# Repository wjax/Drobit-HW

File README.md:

# Drobit-HW
 This repository contains the electronic design and BOM files of the Drobit HW ecosystem.

 Drobit is a PPK (Post Processing Kinematics) solution for the UAV industry. Drobit allows to precisely geotag pictures taken by a camera on board the UAV allowing GCP-free (ground control point) photogrammetry surveys.

 Drobit HW ecosystem is:
 * Drobit Main board
    * Intel Edison CPU
    * Dual-Freq GNSS Board from ComNav
    * 9Dof IMU
    * Batttery management 
 * Drobit Hotshoe board
    * Camera flash signal conditioning
    * 9Dof IMU 
 * Optional: External Button-LED board for cases
 * Optional: Micro connector breakboard

 ## History
 Drobit was created in 2016 by Jose Martinez Rubio and Jesús Alvarez in order to overcome one of the main limitations when doing UAV Photogrammetry applied to big survey areas.... the manual positioning of GCPs.

 Drobit has been used too as *Drobit Inspector* for Civil infrastructure inspection.

 As of today, Drobit has finished its commercial life and we decided to opensource both HW and SW.

 ## Theory of operation
 The idea behind drobit is to provide aerial imagery with super precise WGS84 coordinates of the lens nodal point. If that's the case, photogrammetry software like Agisoft Metashaper or Pix4D can reconstruct the terrain 3D model with centimeter accuracy (with no GCP).

 In order to do that Drobit incorporates a Dual Frequency Survey grade GPS (ComNav 501G) with a Heical Harxon Dual frecuency Antenna that provides 20Hz RAW GNSS observations. We will use Differential GPS as the main source of precise geopositioning.
 It also contains two 9dof IMU, one in the drobit main board and one in the drobit hotshoe board.

 The hotshoe board will be inserted into the camera hotshoe and will provide precise timing for every picture by sensing the flash trigger.

 In a photogrammetry UAV flight, drobit will record GNSS observations (for later postprocessing PPK) and will capture IMU orientation for both drobit main board and hotshoe board.

## Post Processing (PPK and coordinates translation)
 Later, in the office, Drobit PPK Software will obtain precise GPS (WGS84) coordinates from the antenna phase center by resolving the PPK against a GNSS Base receiver (Drobit base or any other manufacturer base with Rinex, even a CORS).

 In order to obtain the nodal camera point position, Drobit PPK Software needs to translate the GNSS antenna coordinate using IMU values and X,Y,Z offsets.

 Once finished, pictures are geotagged and a file containing picture name and precise coordinates is generated.

 Drobit PPK Software creates an kmz for google earth that allows to see cameras oriented and located in 3d space.

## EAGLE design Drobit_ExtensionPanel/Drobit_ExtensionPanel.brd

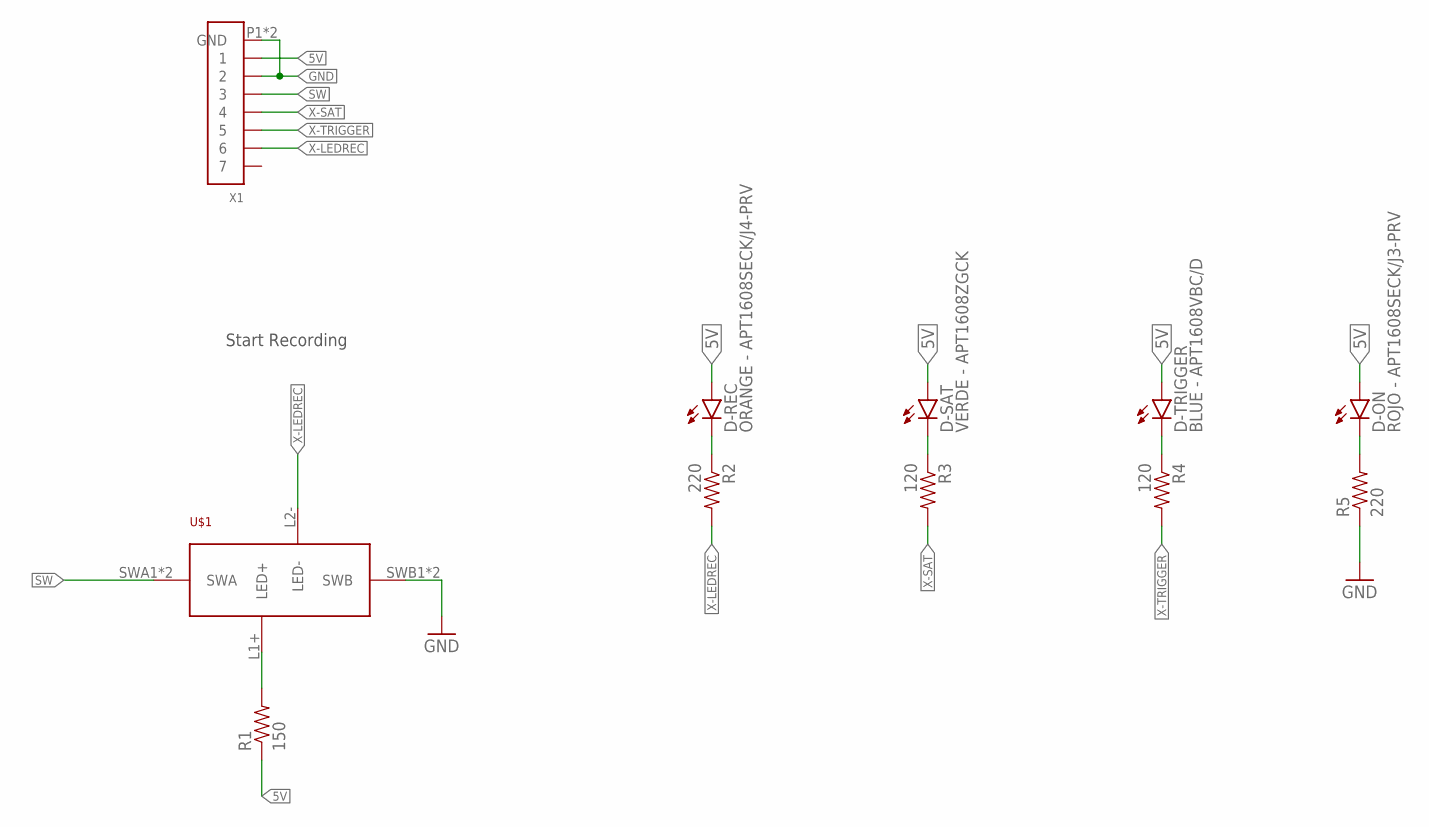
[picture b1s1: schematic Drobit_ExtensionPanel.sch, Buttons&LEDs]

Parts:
D-ON: ROJO - APT1608SECK/J3-PRV; LED3MM; PARTNO 604-APT1608SECKJ3PRV
D-REC: ORANGE - APT1608SECK/J4-PRV; LED3MM; PARTNO 604-APT1608SECKJ4PRV
D-SAT: VERDE - APT1608ZGCK; LED3MM; PARTNO 604-APT1608ZGCK
D-TRIGGER: BLUE - APT1608VBC/D; LED3MM; PARTNO 604-APT1608VBC/D
R1: 150; 1206
R2: 220; 1206; PARTNO 667-ERJ-3GEYJ181V
R3, R4: 120; 1206; PARTNO 667-ERJ-3EKF1050V
R5: 220; 1206; PARTNO 667-ERJ-3EKF82R0V
U$1: PUSH-LED; ITS13FV1ST
X1: CONN_7-1; JST-GH-7

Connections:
5V: D-ON.A, D-REC.A, D-SAT.A, D-TRIGGER.A, R1.1, X1.1
GND: R5.1, U$1.SWB1 (SWB), U$1.SWB2 (SWB), X1.2, X1.P1 (GND), X1.P2 (GND)
unnamed: R1.2, U$1.L1+ (LED+)
unnamed: D-ON.K (C), R5.2
SW: U$1.SWA1 (SWA), U$1.SWA2 (SWA), X1.3
X-LEDREC: R2.2, U$1.L2- (LED-), X1.6
X-LEDREC--: D-REC.K (C), R2.1
X-SAT: R3.2, X1.4
X-SAT--: D-SAT.K (C), R3.1
X-TRIGGER: R4.2, X1.5
X-TRIGGER--: D-TRIGGER.K (C), R4.1

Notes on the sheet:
Start Recording

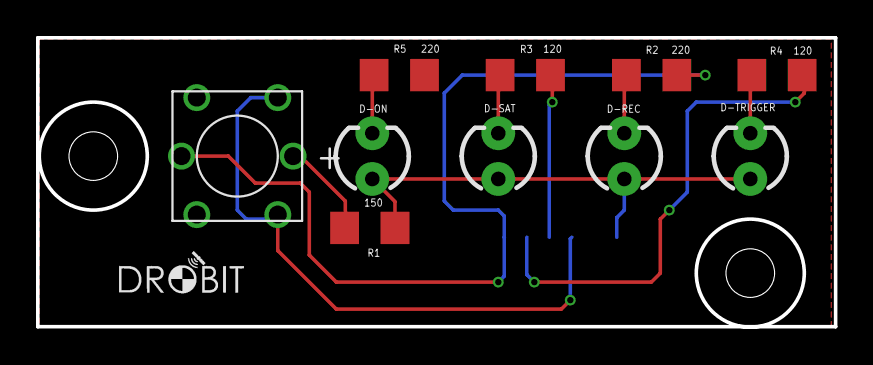
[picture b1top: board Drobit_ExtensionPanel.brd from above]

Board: 2 copper layers, 44.3 x 16.1 mm, 11 parts (1 on the bottom side), 11 nets.

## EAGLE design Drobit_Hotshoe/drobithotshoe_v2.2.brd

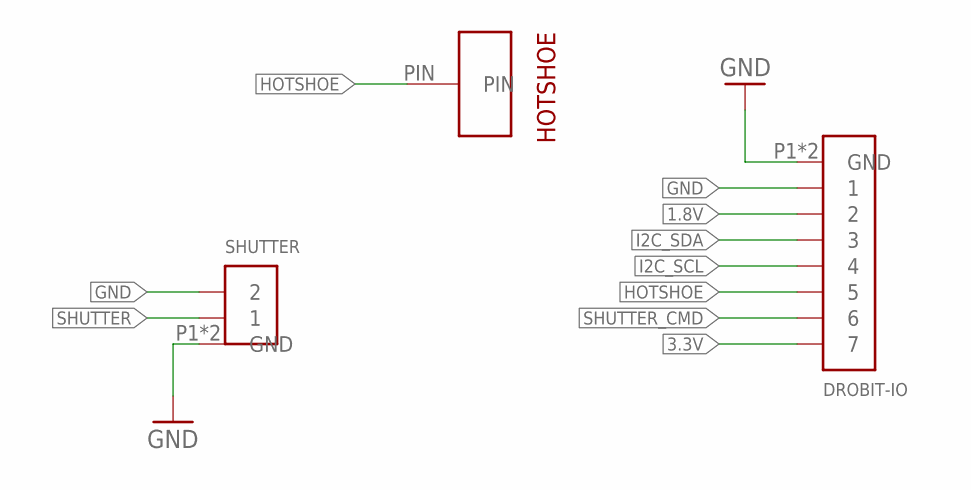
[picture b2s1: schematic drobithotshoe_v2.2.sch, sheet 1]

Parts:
DROBIT-IO: CONN_7-1; JST-GH-7; PARTNO 455-1569-1-ND
HOTSHOE: ZAPATA-MILMAX; MILMAX-807-22-001-30-000101; PARTNO NO_PONER
SHUTTER: CONN_2-1-GH-VERT; JST-GH-2-V; PARTNO 455-1564-1-ND

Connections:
1.8V: DROBIT-IO.2; also elsewhere on the board
3.3V: DROBIT-IO.7; also elsewhere on the board
GND: DROBIT-IO.1, DROBIT-IO.P1 (GND), DROBIT-IO.P2 (GND), SHUTTER.2, SHUTTER.P1 (GND), SHUTTER.P2 (GND); also elsewhere on the board
HOTSHOE: DROBIT-IO.5, HOTSHOE.PIN
I2C_SCL: DROBIT-IO.4; also elsewhere on the board
I2C_SDA: DROBIT-IO.3; also elsewhere on the board
SHUTTER: SHUTTER.1; also elsewhere on the board
SHUTTER_CMD: DROBIT-IO.6; also elsewhere on the board

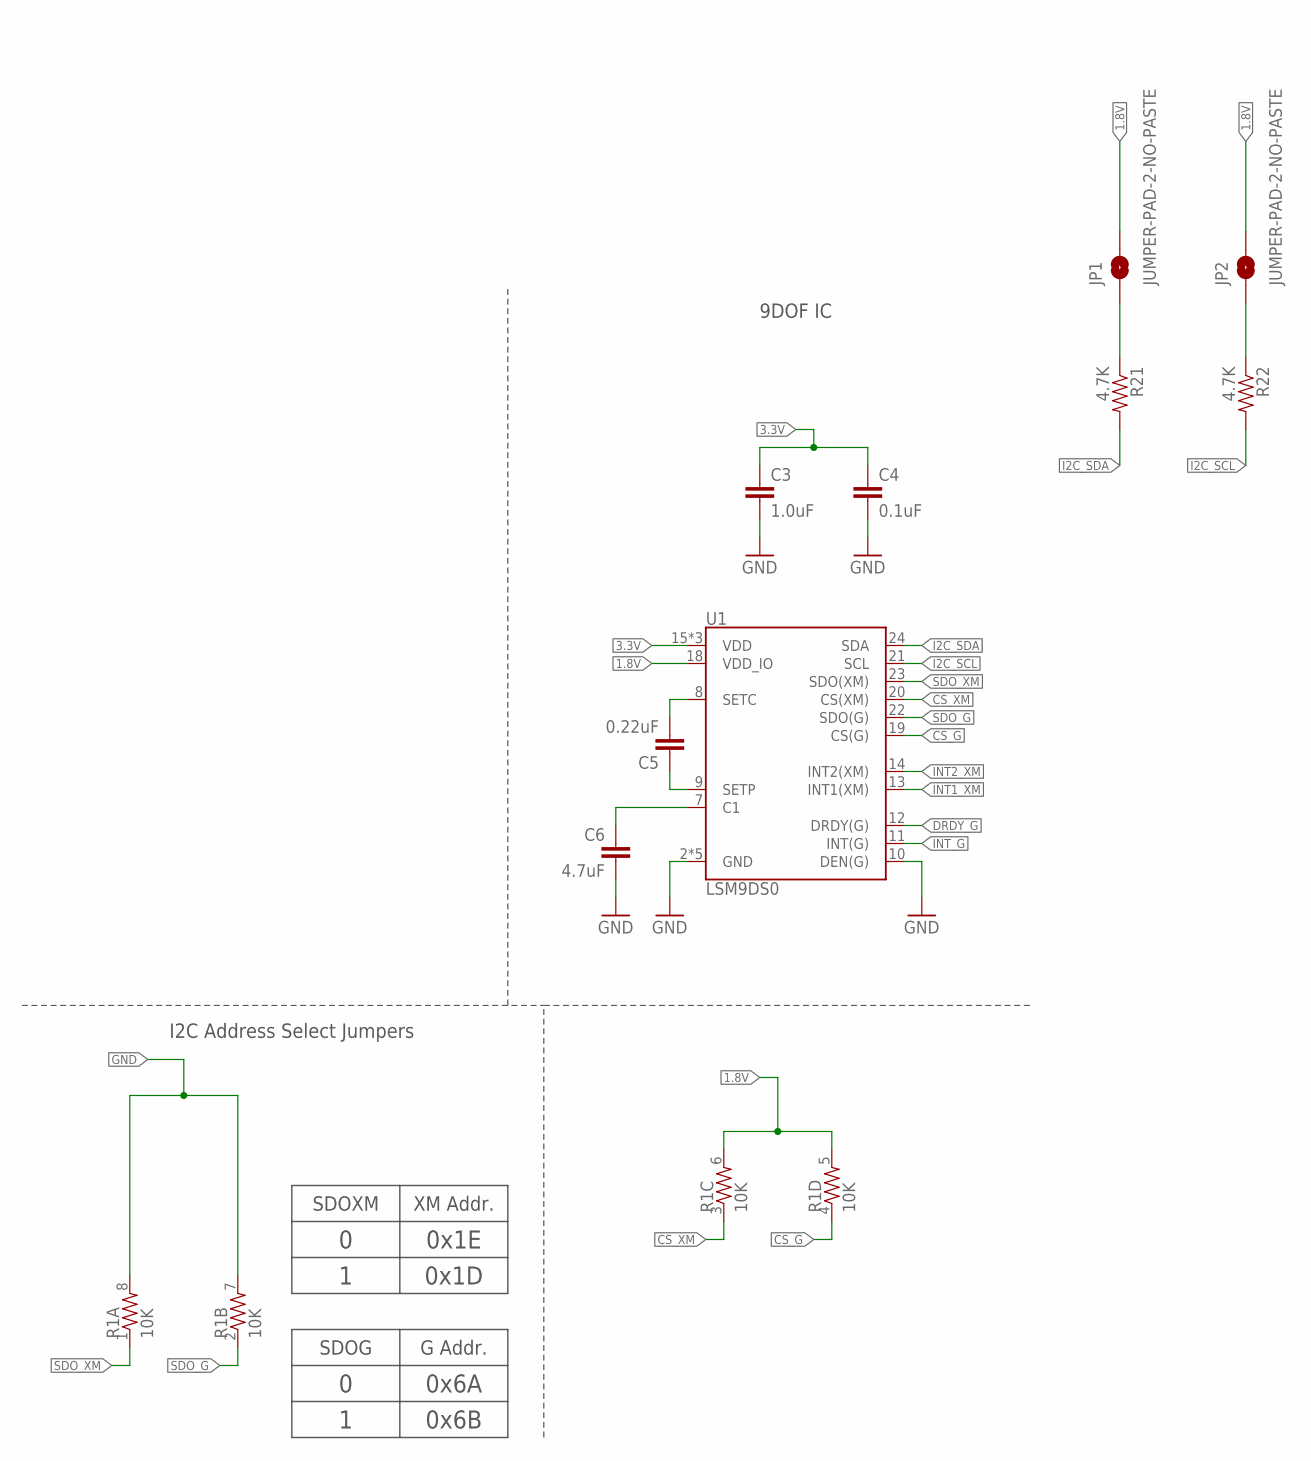
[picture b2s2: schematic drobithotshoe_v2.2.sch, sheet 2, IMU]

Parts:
C3: 1.0uF; 0603-CAP; PARTNO 810-CGA3E1X7R1E105K
C4: 0.1uF; 0603-CAP; PARTNO 810-CGA3E2X7R1E104K
C5: 0.22uF; 0603-CAP; PARTNO 810-C1608X7R1C224K
C6: 4.7uF; 0603-CAP; PARTNO 81-GRM18R60J475KE19D
JP1, JP2: JUMPER-PAD-2-NO-PASTE; PAD-JUMPER-2-NO_NO_SILK_PASTE; PARTNO N/A
R1: 10K; 0603-ARV; PARTNO 667-EXB-38V103JV
R21, R22: 4.7K; 0603-RES; PARTNO 667-ERJ-3GEYJ472V
U1: LSM9DS0; LGA-24; PARTNO 497-13902-1-ND

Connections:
1.8V: JP1.2, JP2.2, R1.5 (2), R1.6 (2), U1.18 (VDD_IO); also elsewhere on the board
3.3V: C3.1, C4.1, U1.15 (VDD), U1.16 (VDD), U1.17 (VDD); also elsewhere on the board
CS_G: R1.4 (1), U1.19 (CS(G))
CS_XM: R1.3 (1), U1.20 (CS(XM))
DRDY_G: U1.12 (DRDY(G))
GND: C3.2, C4.2, C6.2, R1.7 (2), R1.8 (2), U1.2 (GND), U1.3 (GND), U1.4 (GND), U1.5 (GND), U1.6 (GND), U1.10 (DEN(G)); also elsewhere on the board
I2C_SCL: R22.2, U1.21 (SCL); also elsewhere on the board
I2C_SDA: R21.2, U1.24 (SDA); also elsewhere on the board
INT1_XM: U1.13 (INT1(XM))
INT2_XM: U1.14 (INT2(XM))
INT_G: U1.11 (INT(G))
unnamed: C5.1, U1.9 (SETP)
unnamed: C5.2, U1.8 (SETC)
unnamed: C6.1, U1.7 (C1)
unnamed: JP1.1, R21.1
unnamed: JP2.1, R22.1
SDO_G: R1.2 (1), U1.22 (SDO(G))
SDO_XM: R1.1, U1.23 (SDO(XM))

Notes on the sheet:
I2C Address Select Jumpers
9DOF IC
SDOXM
XM Addr.
0x1E
0x1D
SDOG
G Addr.
0x6A
0x6B

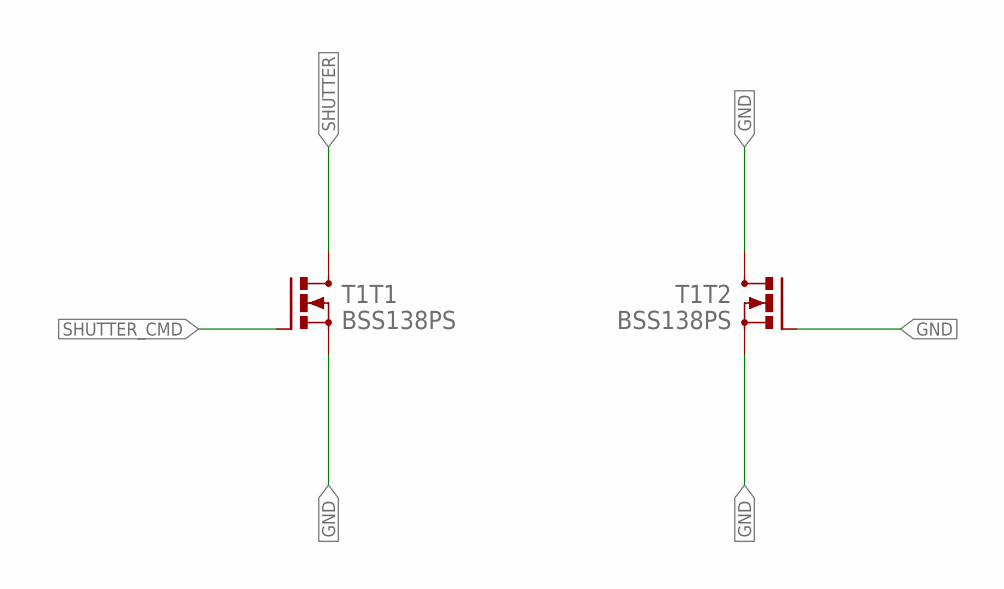
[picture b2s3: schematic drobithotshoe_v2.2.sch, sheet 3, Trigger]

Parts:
T1: BSS138PS; SOT363; PARTNO 771-BSS138BKS115

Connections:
GND: T1.1 (S), T1.3 (D), T1.4 (S), T1.5 (G); also elsewhere on the board
SHUTTER: T1.6 (D); also elsewhere on the board
SHUTTER_CMD: T1.2 (G); also elsewhere on the board

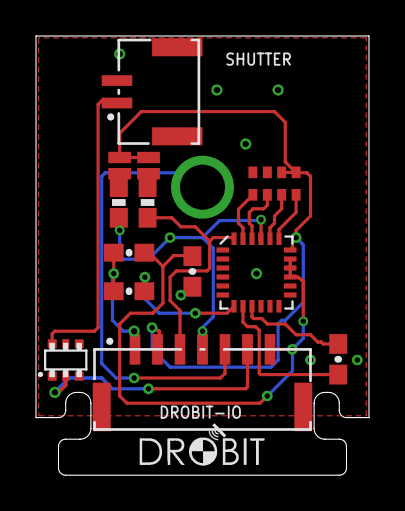
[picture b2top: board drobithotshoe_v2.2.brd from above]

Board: 2 copper layers, 18.5 x 24.4 mm, 14 parts (1 on the bottom side), 17 nets.

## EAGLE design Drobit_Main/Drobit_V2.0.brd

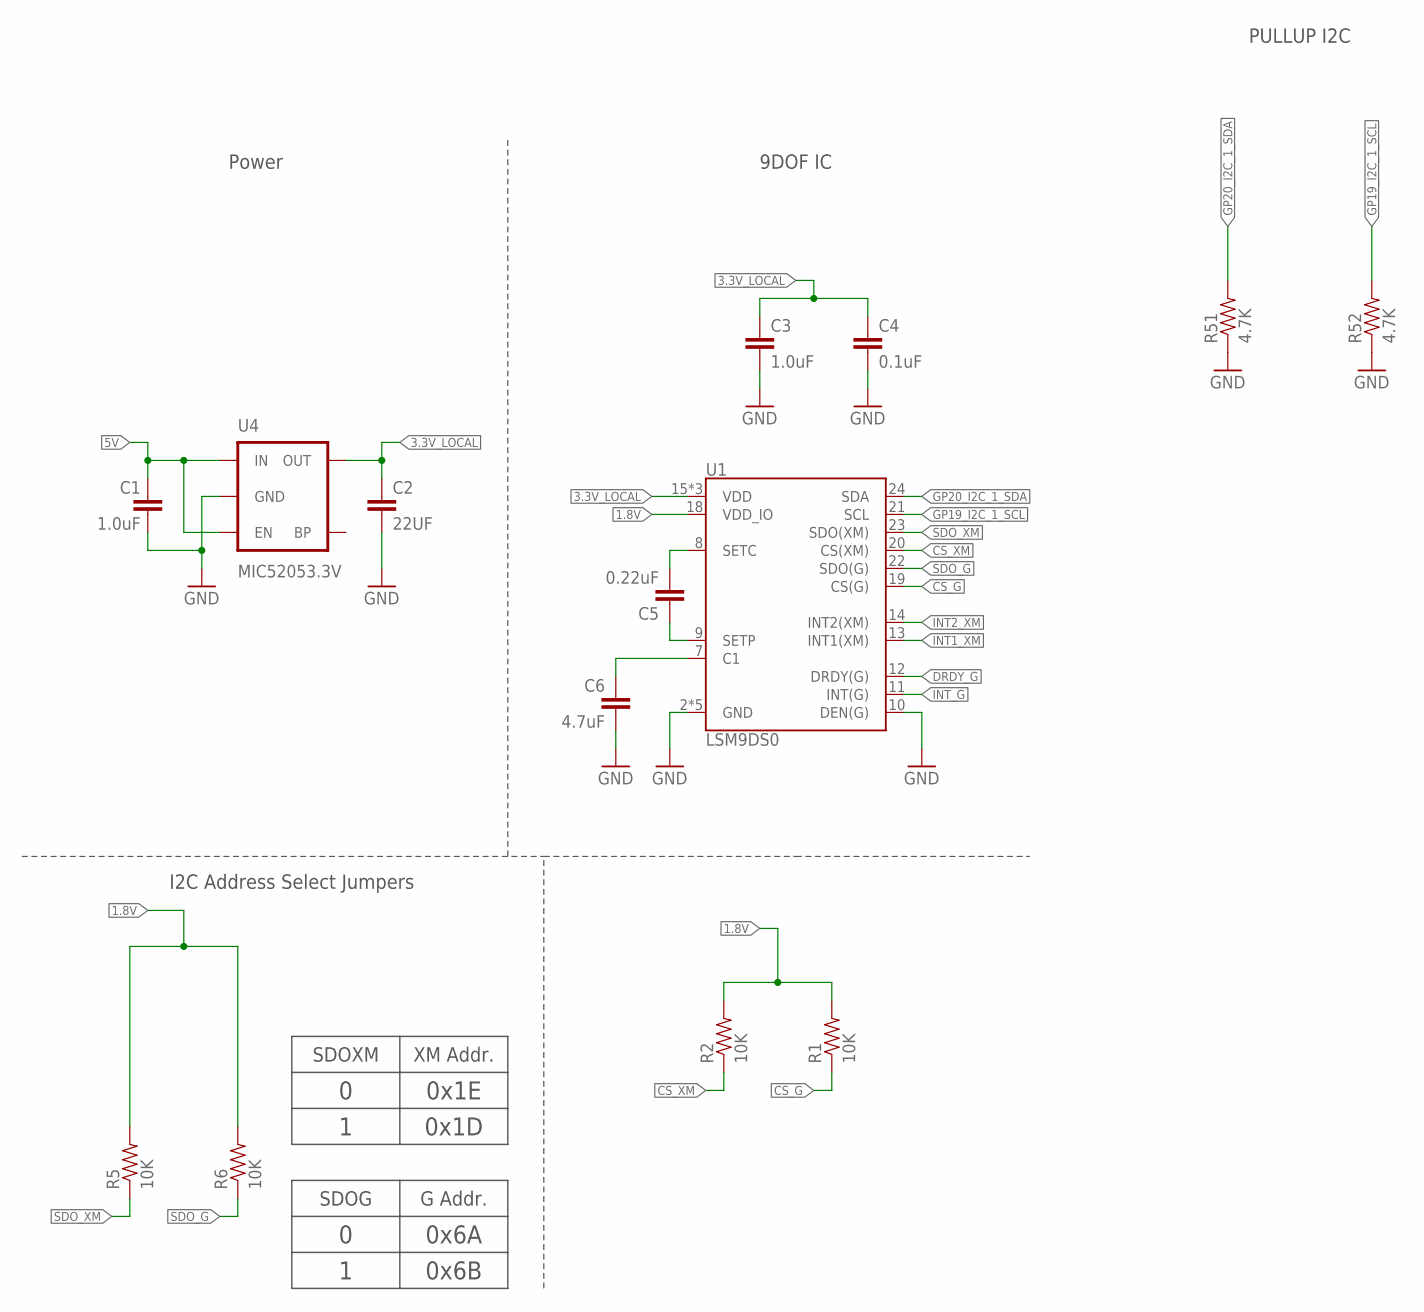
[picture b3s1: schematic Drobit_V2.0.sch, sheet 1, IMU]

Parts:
C1, C3: 1.0uF; 0603-CAP; PARTNO 810-CGA3E1X7R1E105K
C2: 22UF; 0603-CAP; PARTNO 810-C1608X5R1A226M
C4: 0.1uF; 0603-CAP; PARTNO 810-CGA3E2X7R1E104K
C5: 0.22uF; 0603-CAP; PARTNO 810-C1608X7R1C224K
C6: 4.7uF; 0603-CAP; PARTNO 81-GRM18R60J475KE19D
R1, R2, R5, R6: 10K; 0603-RES; PARTNO 667-ERJ-3EKF1002V
R51, R52: 4.7K; 0603-RES; PARTNO NO_PONER
U1: LSM9DS0; LGA-24; PARTNO 497-13902-1-ND
U4: MIC52053.3V; SOT23-5; PARTNO 998-MIC5205-3.3YM5TR

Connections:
1.8V: R1.2, R2.2, R5.2, R6.2, U1.18 (VDD_IO); also elsewhere on the board
3.3V_LOCAL: C2.1, C3.1, C4.1, U1.15 (VDD), U1.16 (VDD), U1.17 (VDD), U4.5 (OUT); also elsewhere on the board
5V: C1.1, U4.1 (IN), U4.3 (EN); also elsewhere on the board
CS_G: R1.1, U1.19 (CS(G))
CS_XM: R2.1, U1.20 (CS(XM))
DRDY_G: U1.12 (DRDY(G))
GND: C1.2, C2.2, C3.2, C4.2, C6.2, R51.1, R52.1, U1.2 (GND), U1.3 (GND), U1.4 (GND), U1.5 (GND), U1.6 (GND), U1.10 (DEN(G)), U4.2 (GND); also elsewhere on the board
GP19_I2C_1_SCL: R52.2, U1.21 (SCL); also elsewhere on the board
GP20_I2C_1_SDA: R51.2, U1.24 (SDA); also elsewhere on the board
INT1_XM: U1.13 (INT1(XM))
INT2_XM: U1.14 (INT2(XM))
INT_G: U1.11 (INT(G))
unnamed: C5.1, U1.9 (SETP)
unnamed: C5.2, U1.8 (SETC)
unnamed: C6.1, U1.7 (C1)
SDO_G: R6.1, U1.22 (SDO(G))
SDO_XM: R5.1, U1.23 (SDO(XM))

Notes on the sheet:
I2C Address Select Jumpers
9DOF IC
Power
SDOXM
XM Addr.
0x1E
0x1D
SDOG
G Addr.
0x6A
0x6B
PULLUP I2C

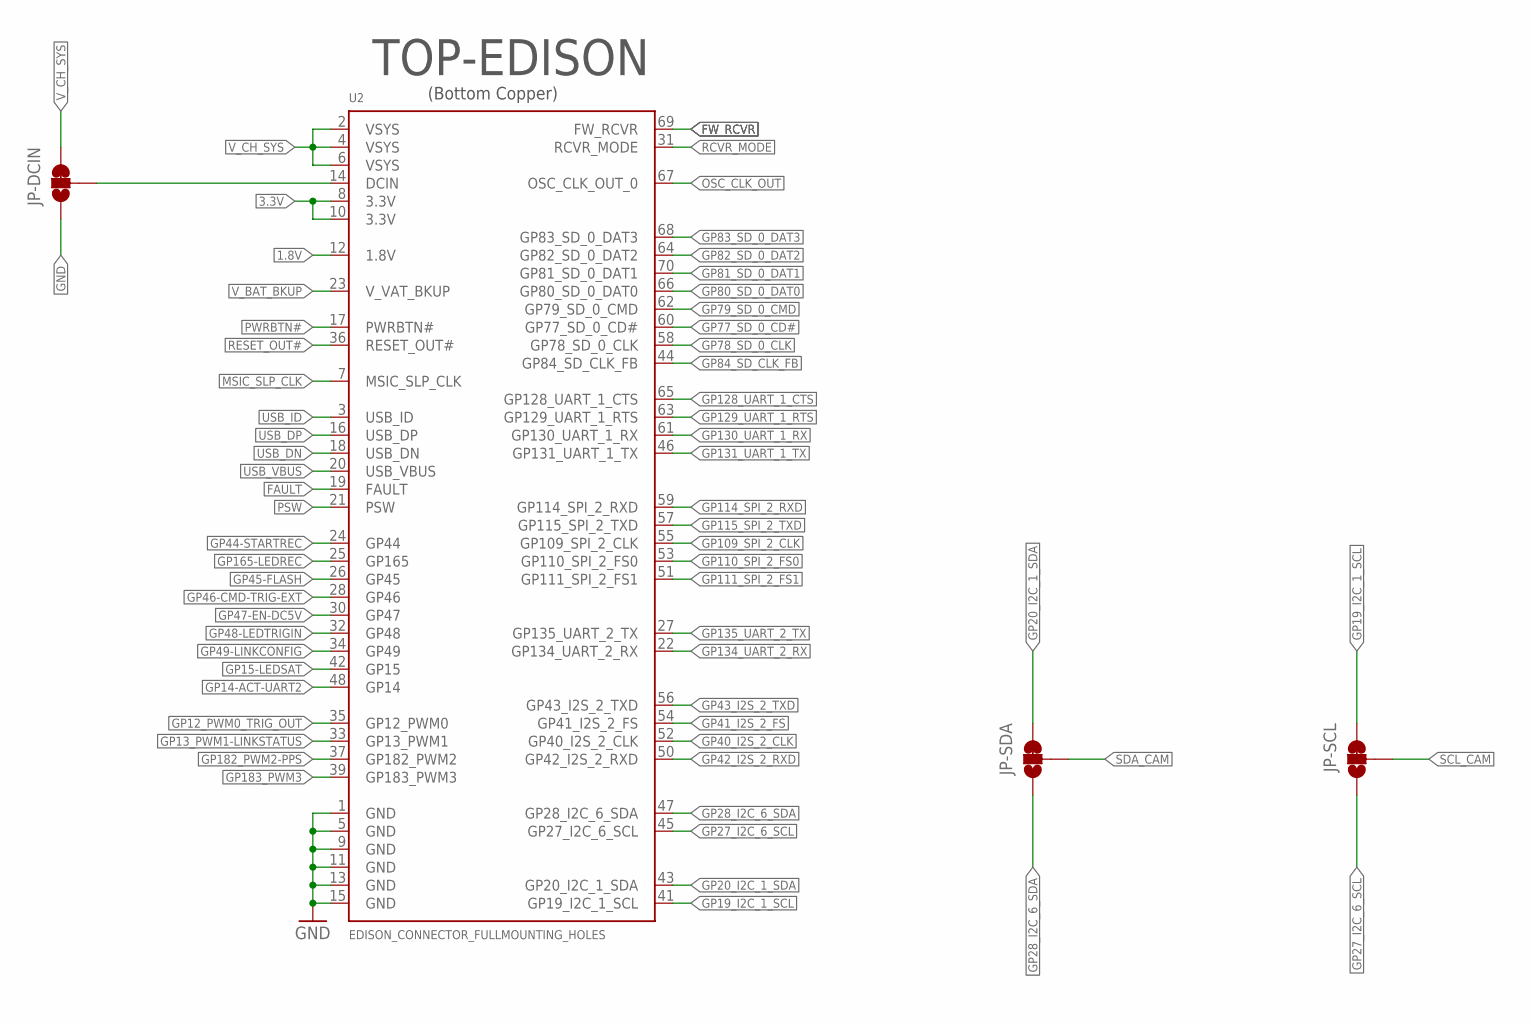
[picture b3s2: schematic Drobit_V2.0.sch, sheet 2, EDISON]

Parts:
JP-DCIN: JUMPER-PAD-3-2OF3_NC_BY_TRACE_SMALL; PAD-JUMPER-3-2OF3_NC_BY_TRACE_YES_SILK_FULL_BOX
JP-SCL: JUMPER-PAD-3-2OF3_NC_BY_TRACE_SMALL; PAD-JUMPER-3-2OF3_NC_BY_TRACE_YES_SILK_FULL_BOX
JP-SDA: JUMPER-PAD-3-2OF3_NC_BY_TRACE_SMALL; PAD-JUMPER-3-2OF3_NC_BY_TRACE_YES_SILK_FULL_BOX
U2: EDISON_CONNECTOR_FULLMOUNTING_HOLES; EDISON_DAUGHTER; PARTNO 798-DF40C70DS04V51

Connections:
1.8V: U2.12 (1.8V); also elsewhere on the board
3.3V: U2.8 (3.3V), U2.10 (3.3V); also elsewhere on the board
FAULT: U2.19 (FAULT); also elsewhere on the board
FW_RCVR: U2.69 (FW_RCVR)
GND: JP-DCIN.1, U2.1 (GND), U2.5 (GND), U2.9 (GND), U2.11 (GND), U2.13 (GND), U2.15 (GND); also elsewhere on the board
GP12_PWM0_TRIG_OUT: U2.35 (GP12_PWM0); also elsewhere on the board
GP13_PWM1-LINKSTATUS: U2.33 (GP13_PWM1); also elsewhere on the board
GP14-ACT-UART2: U2.48 (GP14); also elsewhere on the board
GP15-LEDSAT: U2.42 (GP15); also elsewhere on the board
GP19_I2C_1_SCL: JP-SCL.3, U2.41 (GP19_I2C_1_SCL); also elsewhere on the board
GP20_I2C_1_SDA: JP-SDA.3, U2.43 (GP20_I2C_1_SDA); also elsewhere on the board
GP27_I2C_6_SCL: JP-SCL.1, U2.45 (GP27_I2C_6_SCL)
GP28_I2C_6_SDA: JP-SDA.1, U2.47 (GP28_I2C_6_SDA)
GP40_I2S_2_CLK: U2.52 (GP40_I2S_2_CLK)
GP41_I2S_2_FS: U2.54 (GP41_I2S_2_FS)
GP42_I2S_2_RXD: U2.50 (GP42_I2S_2_RXD)
GP43_I2S_2_TXD: U2.56 (GP43_I2S_2_TXD)
GP44-STARTREC: U2.24 (GP44); also elsewhere on the board
GP45-FLASH: U2.26 (GP45); also elsewhere on the board
GP46-CMD-TRIG-EXT: U2.28 (GP46); also elsewhere on the board
GP47-EN-DC5V: U2.30 (GP47); also elsewhere on the board
GP48-LEDTRIGIN: U2.32 (GP48); also elsewhere on the board
GP49-LINKCONFIG: U2.34 (GP49); also elsewhere on the board
GP77_SD_0_CD#: U2.60 (GP77_SD_0_CD#); also elsewhere on the board
GP78_SD_0_CLK: U2.58 (GP78_SD_0_CLK); also elsewhere on the board
GP79_SD_0_CMD: U2.62 (GP79_SD_0_CMD); also elsewhere on the board
GP80_SD_0_DAT0: U2.66 (GP80_SD_0_DAT0); also elsewhere on the board
GP81_SD_0_DAT1: U2.70 (GP81_SD_0_DAT1); also elsewhere on the board
GP82_SD_0_DAT2: U2.64 (GP82_SD_0_DAT2); also elsewhere on the board
GP83_SD_0_DAT3: U2.68 (GP83_SD_0_DAT3); also elsewhere on the board
GP84_SD_CLK_FB: U2.44 (GP84_SD_CLK_FB); also elsewhere on the board
GP109_SPI_2_CLK: U2.55 (GP109_SPI_2_CLK)
GP110_SPI_2_FS0: U2.53 (GP110_SPI_2_FS0)
GP111_SPI_2_FS1: U2.51 (GP111_SPI_2_FS1)
GP114_SPI_2_RXD: U2.59 (GP114_SPI_2_RXD)
GP115_SPI_2_TXD: U2.57 (GP115_SPI_2_TXD)
GP128_UART_1_CTS: U2.65 (GP128_UART_1_CTS)
GP129_UART_1_RTS: U2.63 (GP129_UART_1_RTS)
GP130_UART_1_RX: U2.61 (GP130_UART_1_RX); also elsewhere on the board
GP131_UART_1_TX: U2.46 (GP131_UART_1_TX); also elsewhere on the board
GP134_UART_2_RX: U2.22 (GP134_UART_2_RX); also elsewhere on the board
GP135_UART_2_TX: U2.27 (GP135_UART_2_TX); also elsewhere on the board
GP165-LEDREC: U2.25 (GP165); also elsewhere on the board
GP182_PWM2-PPS: U2.37 (GP182_PWM2); also elsewhere on the board
GP183_PWM3: U2.39 (GP183_PWM3)
MSIC_SLP_CLK: U2.7 (MSIC_SLP_CLK)
unnamed: JP-DCIN.2, U2.14 (DCIN)
OSC_CLK_OUT: U2.67 (OSC_CLK_OUT_0)
PSW: U2.21 (PSW); also elsewhere on the board
PWRBTN#: U2.17 (PWRBTN#); also elsewhere on the board
RCVR_MODE: U2.31 (RCVR_MODE)
RESET_OUT#: U2.36 (RESET_OUT#)
SCL_CAM: JP-SCL.2; also elsewhere on the board
SDA_CAM: JP-SDA.2; also elsewhere on the board
USB_DN: U2.18 (USB_DN); also elsewhere on the board
USB_DP: U2.16 (USB_DP); also elsewhere on the board
USB_ID: U2.3 (USB_ID); also elsewhere on the board
USB_VBUS: U2.20 (USB_VBUS); also elsewhere on the board
V_BAT_BKUP: U2.23 (V_VAT_BKUP)
V_CH_SYS: JP-DCIN.3, U2.2 (VSYS), U2.4 (VSYS), U2.6 (VSYS); also elsewhere on the board

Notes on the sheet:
TOP-EDISON
(Bottom Copper)

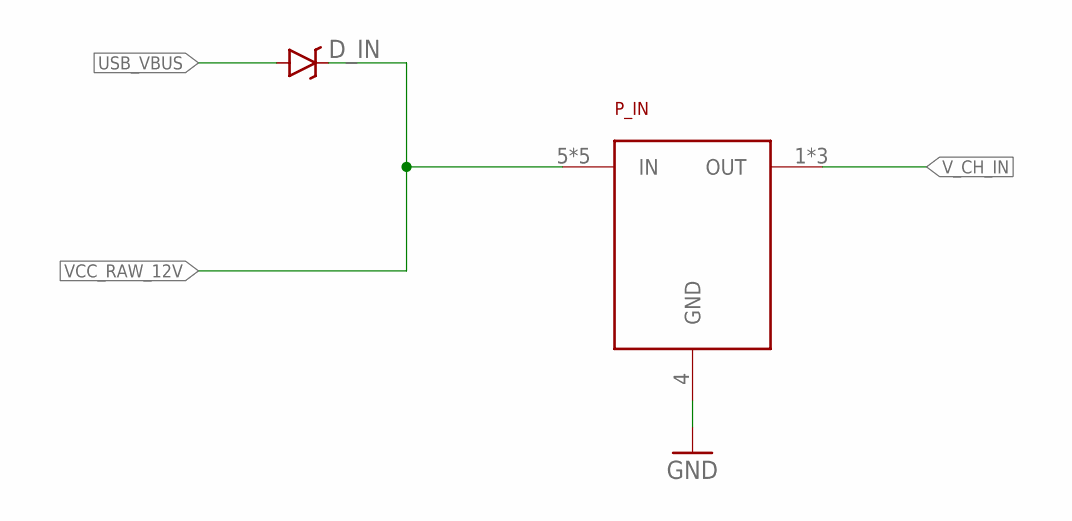
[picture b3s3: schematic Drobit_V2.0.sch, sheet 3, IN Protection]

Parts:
D_IN: V8PAN50-M3/I; PARTNO NO_PONER
P_IN: FR014H5JZ; PARTNO 512-FR014H5JZ

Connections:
GND: P_IN.4 (GND); also elsewhere on the board
USB_VBUS: D_IN.A; also elsewhere on the board
VCC_RAW_12V: D_IN.C, P_IN.5 (IN), P_IN.6 (IN), P_IN.7 (IN), P_IN.8 (IN), P_IN.PAD (IN); also elsewhere on the board
V_CH_IN: P_IN.1 (OUT), P_IN.2 (OUT), P_IN.3 (OUT); also elsewhere on the board

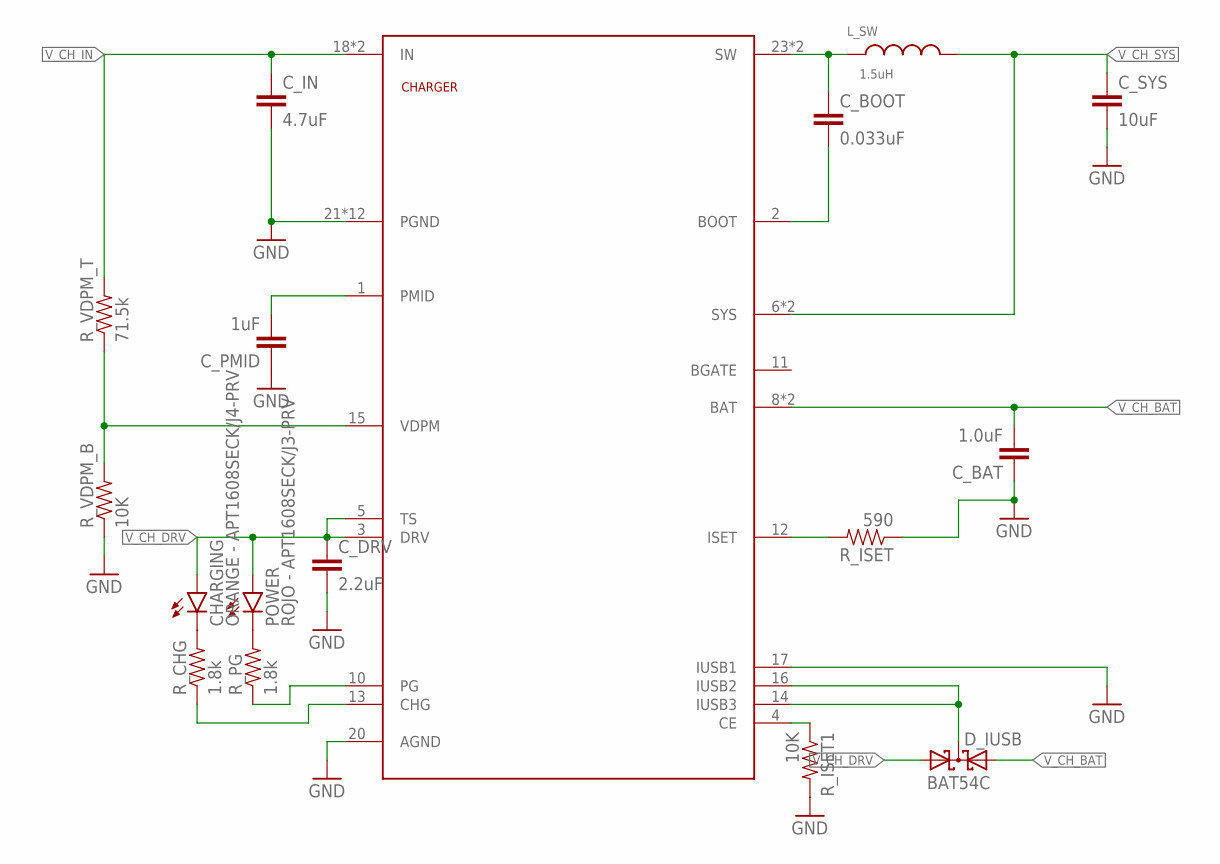
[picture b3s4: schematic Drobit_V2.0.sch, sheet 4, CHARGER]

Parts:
CHARGER: BQ24266; QFN50P400X400X100-25N; PARTNO 595-BQ24266RGER
CHARGING: ORANGE - APT1608SECK/J4-PRV; LED-0603; PARTNO 604-APT1608SECKJ4PRV
C_BAT: 1.0uF; 0603-CAP; PARTNO 810-CGA3E1X7R1E105K
C_BOOT: 0.033uF; 0603-CAP; PARTNO 810-CGA3E2X7R1H333MA
C_DRV: 2.2uF; 0603-CAP; PARTNO 810-CGA3E1X5R1C225K
C_IN: 4.7uF; 0603-CAP; PARTNO 810-C2012X5R1E226M
C_PMID: 1uF; 0603-CAP; PARTNO 810-CGA3E1X7R1E105K
C_SYS: 10uF; 1210; PARTNO 810-C3225X7R1E106K
D_IUSB: BAT54C; SOT23; PARTNO 512-BAT54C
L_SW: 1.5uH; FDSD0420; PARTNO 81-FDSD0420-H-1R5MP3
POWER: ROJO - APT1608SECK/J3-PRV; LED-0603; PARTNO 604-APT1608SECKJ3PRV
R_CHG: 1.8k; 0603-RES; PARTNO 667-ERJ-3GEYJ182V
R_ISET: 590; 0603-RES; PARTNO 754-RR0816P-5900D75A
R_ISET1: 10K; 0603-RES; PARTNO 667-ERJ-3EKF1002V
R_PG: 1.8k; 0603-RES; PARTNO 667-ERJ-3GEYJ182V
R_VDPM_B: 10K; 0603-RES; PARTNO 667-ERJ-3EKF1002V
R_VDPM_T: 71.5k; 0603-RES; PARTNO 667-ERJ-3EKF7152V

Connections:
GND: CHARGER.17 (IUSB1), CHARGER.20 (AGND), CHARGER.21 (PGND), CHARGER.22 (PGND), CHARGER.25 (PGND), CHARGER.P$2 (PGND), CHARGER.P$3 (PGND), CHARGER.P$4 (PGND), CHARGER.P$5 (PGND), CHARGER.P$6 (PGND), CHARGER.P$7 (PGND), CHARGER.P$8 (PGND), CHARGER.P$9 (PGND), CHARGER.P$10 (PGND), C_BAT.1, C_DRV.2, C_IN.2, C_PMID.1, C_SYS.2, R_ISET.1, R_ISET1.2, R_VDPM_B.1; also elsewhere on the board
unnamed: CHARGER.4 (CE), R_ISET1.1
unnamed: POWER.C, R_PG.2
unnamed: CHARGING.C, R_CHG.2
unnamed: CHARGER.10 (PG), R_PG.1
unnamed: CHARGER.13 (CHG), R_CHG.1
unnamed: CHARGER.2 (BOOT), C_BOOT.2
unnamed: CHARGER.12 (ISET), R_ISET.2
unnamed: CHARGER.14 (IUSB3), CHARGER.16 (IUSB2), D_IUSB.3 (CC)
V_CH_BAT: CHARGER.8 (BAT), CHARGER.9 (BAT), C_BAT.2, D_IUSB.2 (A2); also elsewhere on the board
V_CH_DPM: CHARGER.15 (VDPM), R_VDPM_B.2, R_VDPM_T.1
V_CH_DRV: CHARGER.3 (DRV), CHARGER.5 (TS), CHARGING.A, C_DRV.1, D_IUSB.1 (A1), POWER.A
V_CH_IN: CHARGER.18 (IN), CHARGER.19 (IN), C_IN.1, R_VDPM_T.2; also elsewhere on the board
V_CH_PMID: CHARGER.1 (PMID), C_PMID.2
V_CH_SW: CHARGER.23 (SW), CHARGER.24 (SW), C_BOOT.1, L_SW.1
V_CH_SYS: CHARGER.6 (SYS), CHARGER.7 (SYS), C_SYS.1, L_SW.2; also elsewhere on the board

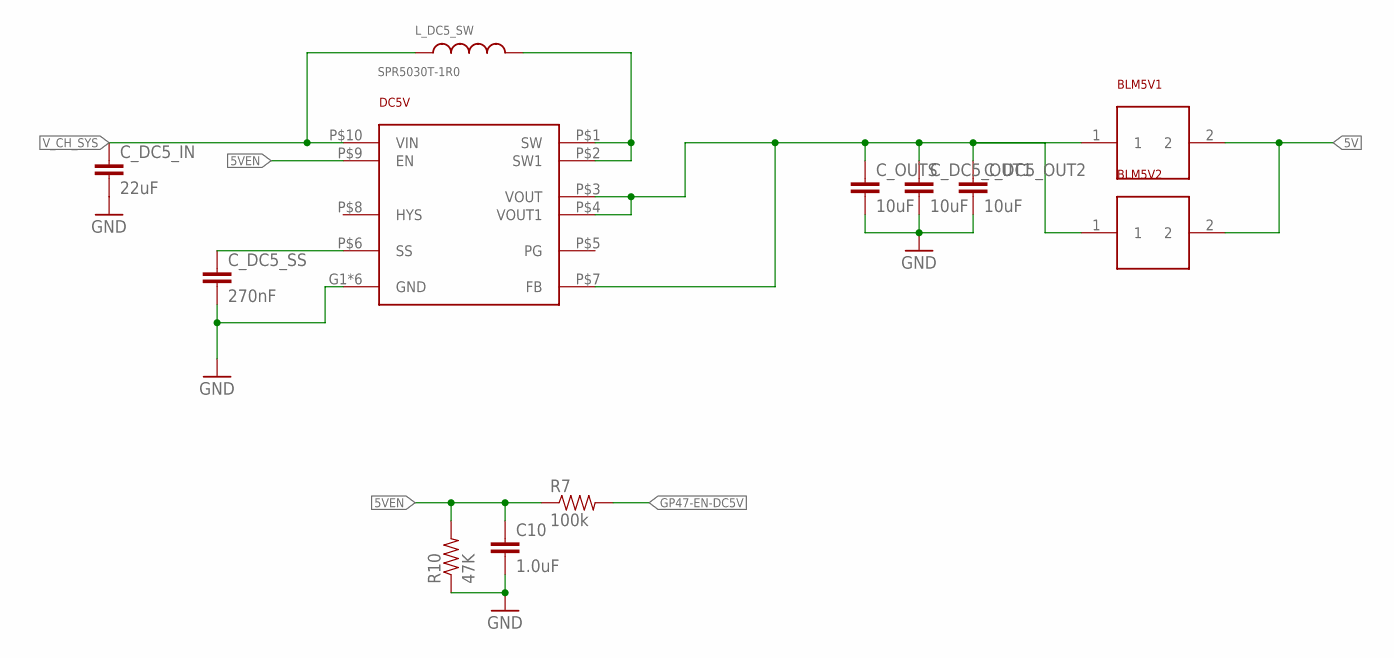
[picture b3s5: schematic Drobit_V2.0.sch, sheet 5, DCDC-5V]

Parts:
BLM5V1, BLM5V2: BLM18SG221TZ1-2.5A; 0603; PARTNO 81-BLM18SG221TZ1D
C10: 1.0uF; 0603-CAP; PARTNO 810-CGA3E1X7R1E105K
C_DC5_IN: 22uF; 1210; PARTNO 81-GRM32ER61E226ME5L
C_DC5_OUT1, C_DC5_OUT2: 10uF; 1210; PARTNO 810-C3225X7R1E106K
C_DC5_SS: 270nF; 0603-CAP; PARTNO 81-GRM188R71C274KA1D
C_OUTS: 10uF; 1210; PARTNO 810-C3225X7R1E106K
DC5V: TPS61232; SON-10; PARTNO 595-TPS61232DRCR
L_DC5_SW: SPR5030T-1R0; SRP5030T-1R0; PARTNO 652-SRP5030T-1R0M
R7: 100k; 0603-RES; PARTNO 594-MCT06030C1003FP5
R10: 47K; 0603-RES; PARTNO NO_PONER

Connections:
5V: BLM5V1.2, BLM5V2.2; also elsewhere on the board
5VEN: C10.1, DC5V.P$9 (EN), R7.1, R10.2
5VRAW: BLM5V1.1, BLM5V2.1, C_DC5_OUT1.1, C_DC5_OUT2.1, C_OUTS.1, DC5V.P$3 (VOUT), DC5V.P$4 (VOUT1), DC5V.P$7 (FB)
GND: C10.2, C_DC5_IN.2, C_DC5_OUT1.2, C_DC5_OUT2.2, C_DC5_SS.2, C_OUTS.2, DC5V.G1 (GND), DC5V.G2 (GND), DC5V.G3 (GND), DC5V.G4 (GND), DC5V.G5 (GND), DC5V.PAD (GND), R10.1; also elsewhere on the board
GP47-EN-DC5V: R7.2; also elsewhere on the board
V_CH_SYS: C_DC5_IN.1, DC5V.P$10 (VIN), L_DC5_SW.P$1 (1); also elsewhere on the board
V_DC5_SS: C_DC5_SS.1, DC5V.P$6 (SS)
V_DC5_SW: DC5V.P$1 (SW), DC5V.P$2 (SW1), L_DC5_SW.P$2 (2)

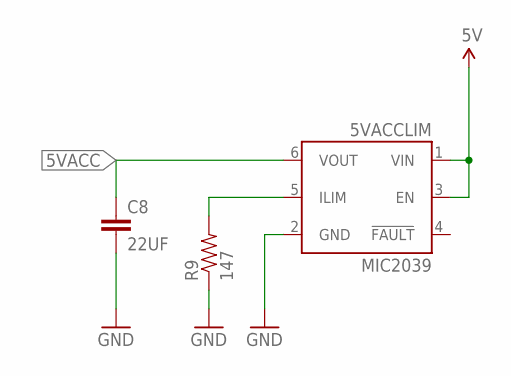
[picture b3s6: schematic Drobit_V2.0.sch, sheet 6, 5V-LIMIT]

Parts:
5VACCLIM: MIC2039; SOT23-6; PARTNO 998-MIC2039EYM6T5
C8: 22UF; 0603-CAP; PARTNO 810-C1608X5R1A226M
R9: 147; 0603-RES; PARTNO 754-RR0816P-1470D17A

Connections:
5V: 5VACCLIM.1 (VIN), 5VACCLIM.3 (EN); also elsewhere on the board
5VACC: 5VACCLIM.6 (VOUT), C8.1; also elsewhere on the board
GND: 5VACCLIM.2 (GND), C8.2, R9.1; also elsewhere on the board
unnamed: 5VACCLIM.5 (ILIM), R9.2

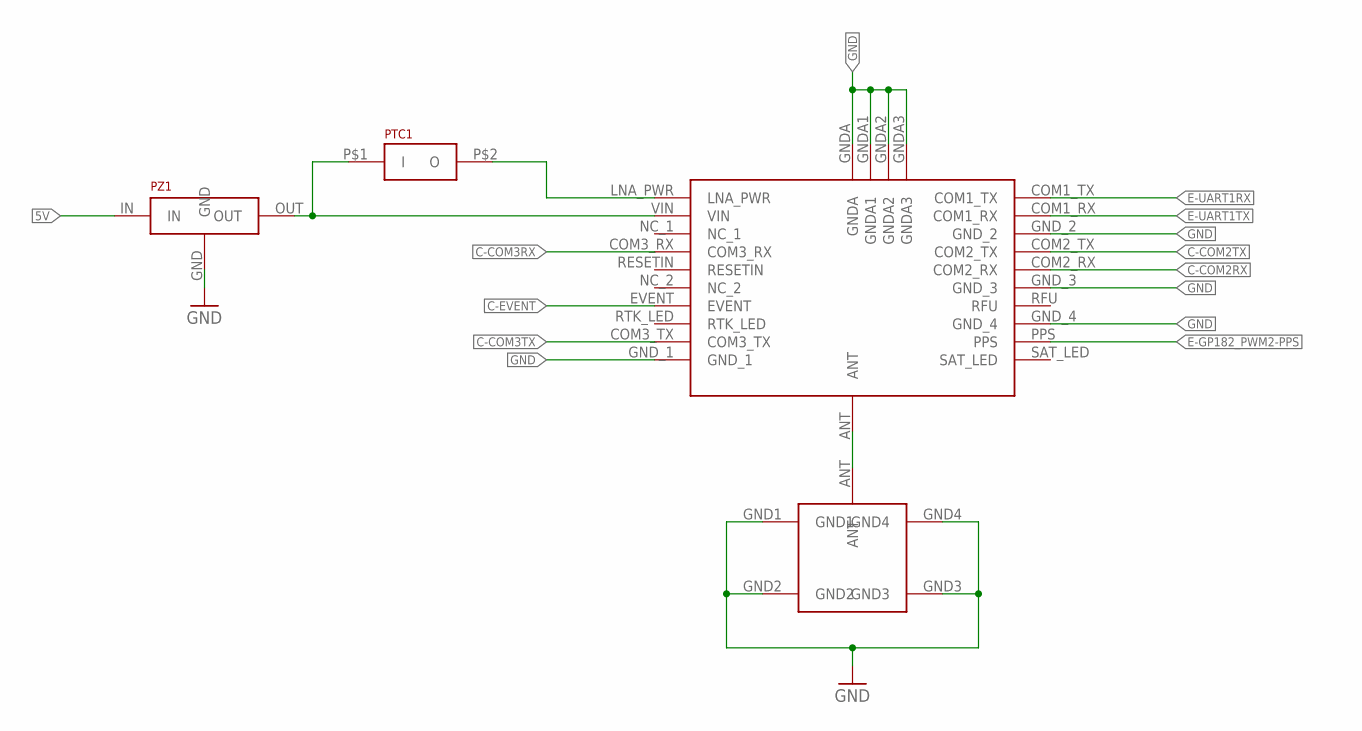
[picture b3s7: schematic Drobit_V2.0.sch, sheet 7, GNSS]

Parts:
PTC1: 0603L010YR; 0602; PARTNO 576-0603L010YR
PZ1: ZEN056V230A16YC; PARTNO 650-ZEN056V230A16YC
U$1: COMNAV_501G
U$2: MCX-TECON-1-1337586-0; 1-1337586-0; PARTNO 571-1-1337586-0

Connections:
5V: PZ1.IN; also elsewhere on the board
C-COM2RX: U$1.COM2_RX; also elsewhere on the board
C-COM2TX: U$1.COM2_TX; also elsewhere on the board
C-COM3RX: U$1.COM3_RX
C-COM3TX: U$1.COM3_TX
C-EVENT: U$1.EVENT; also elsewhere on the board
E-GP182_PWM2-PPS: U$1.PPS; also elsewhere on the board
E-UART1RX: U$1.COM1_TX; also elsewhere on the board
E-UART1TX: U$1.COM1_RX; also elsewhere on the board
GND: PZ1.GND, U$1.GNDA, U$1.GNDA1, U$1.GNDA2, U$1.GNDA3, U$1.GND_1, U$1.GND_2, U$1.GND_3, U$1.GND_4, U$2.GND1, U$2.GND2, U$2.GND3, U$2.GND4; also elsewhere on the board
unnamed: PTC1.P$2 (O), U$1.LNA_PWR
unnamed: PTC1.P$1 (I), PZ1.OUT, U$1.VIN
unnamed: U$1.ANT, U$2.ANT

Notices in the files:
parts and their libraries:
SparkFun-LED: Licensing: Creative Commons ShareAlike 4.0 International - https://creativecommons.org/licenses/by-sa/4.0
SparkFun-DigitalIC: Licensing: CC v3.0 Share-Alike You are welcome to use this library for commercial purposes.
